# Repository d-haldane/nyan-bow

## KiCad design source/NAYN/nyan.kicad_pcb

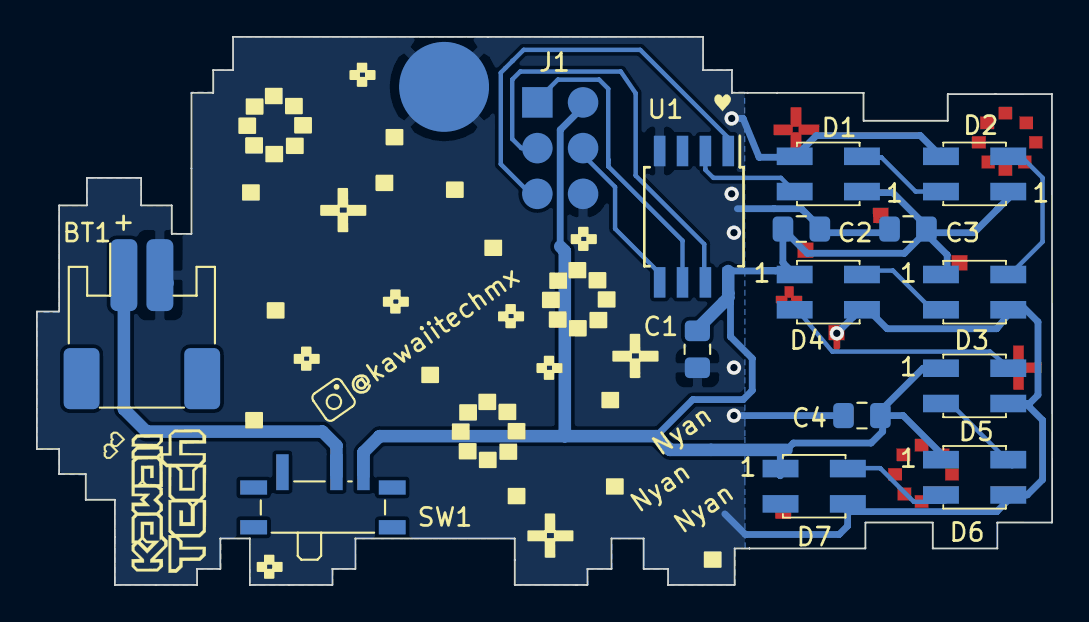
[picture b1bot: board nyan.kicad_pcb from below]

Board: 2 copper layers, 56.4 x 30.4 mm, 20 parts (19 on the bottom side), 14 nets.

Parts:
BT1: Battery; JST_PH_S2B-PH-SM4-TB_1x02-1MP_P2.00mm_Horizontal
C1, C2, C3, C4: 0.1u; C_0805_2012Metric_Pad1.15x1.40mm_HandSolder
D1, D2, D3, D4, D5, D6, D7: WS2812B; LED_WS2812B_mini3535
J1: Conn_02x03_Male_DNI; PinHeader_2x03_P2.54mm_Vertical_SMDcircular
Ref**: Val**; nyancat
Ref**#2: Val**; pinIndicatorHeart
SW1: SW_SPDT; SW_SPDT_PCM12_SMDHOLE
U1: ATtiny85-20SU; SOIJ-8_5.3x5.3mm_P1.27mm
svg2mod: G***; instagram
svg2mod#2: G***; logoCorazones
svg2mod#3: G***; KawaiiTechLogo

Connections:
+BATT: BT1.1, SW1.2
/MISO_PIN1: J1.1, U1.6
/MOSI_PIN0: J1.4, U1.5
/N_RESET: J1.5, U1.1
/SCK_PIN2: J1.3, U1.7
/VCC: C1.1, C2.1, C3.1, C4.1, D1.1, D2.1, D3.1, D4.1, D5.1, D6.1, D7.1, J1.2, SW1.3, U1.8
GND: BT1.2, C1.2, C2.2, C3.2, C4.2, D1.3, D2.3, D3.3, D4.3, D5.3, D6.3, D7.3, J1.6, U1.4
unnamed: D1.2, D2.4
unnamed: D1.4, U1.2
unnamed: D2.2, D3.4
unnamed: D3.2, D4.4
unnamed: D4.2, D5.4
unnamed: D5.2, D6.4
unnamed: D6.2, D7.4

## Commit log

2022-07-01 Adding imports, most LEDs are arranged.
2023-05-09 Big reorg. Submodule hackathon
2023-05-09 Update design outline
2023-05-10 Parts mostly added
2023-05-10 Most things connected
2023-07-19 Updated version
2023-09-06 add firmware
